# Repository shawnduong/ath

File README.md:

# ath.ino

ath.ino is a simple circuit board that displays a binary message with LEDs, one nibble at a time. This was my first time creating a PCB and this project mainly serves as educational experience and material.

## Images

(The 5V voltage regulator is not needed for this project. It is shown in mine because my Arduino's onboard voltage regulator is broken. See the note at the bottom of this README.)

## Schematic

## Materials

To create this project, you need:

1. 1x Arduino Pro Mini
2. 1x SN74HC595N Shift Register
3. 3x 100 Ohm resistors
   - Other resistor values will substitute just fine depending on the maximum brightness you want for the LEDs.
4. 4x 2n2222 transistors
   - Other transistors can substitute as long as the middle pin is the base.
5. 3x Push buttons
6. 1x Micro slide switches
7. 1x 4x AAAA battery holder
8. 4x RGB common cathode LEDs

## Instructions

1. Print the PCB and solder the parts according to the schematics. The schematics can be viewed in a PCB CAD program such as KiCAD.
2. Upload the code in `src/ath.ino`. Change the `byte sequence[]` variable to be your desired values.

## Usage

Power the LED on by flipping the power switch (PSW0). Dim the R, G, and B levels by pushing SW0, SW1, and SW2, respectively. After reaching the minimum dimness level, the color channel will loop back to the maximum.

## Note

If the onboard voltage regulator in the Arduino is broken, you can connect a 5V voltage regulator the VIN/GND of the Arduino and connect Vout to the 5V line in the Arduino.

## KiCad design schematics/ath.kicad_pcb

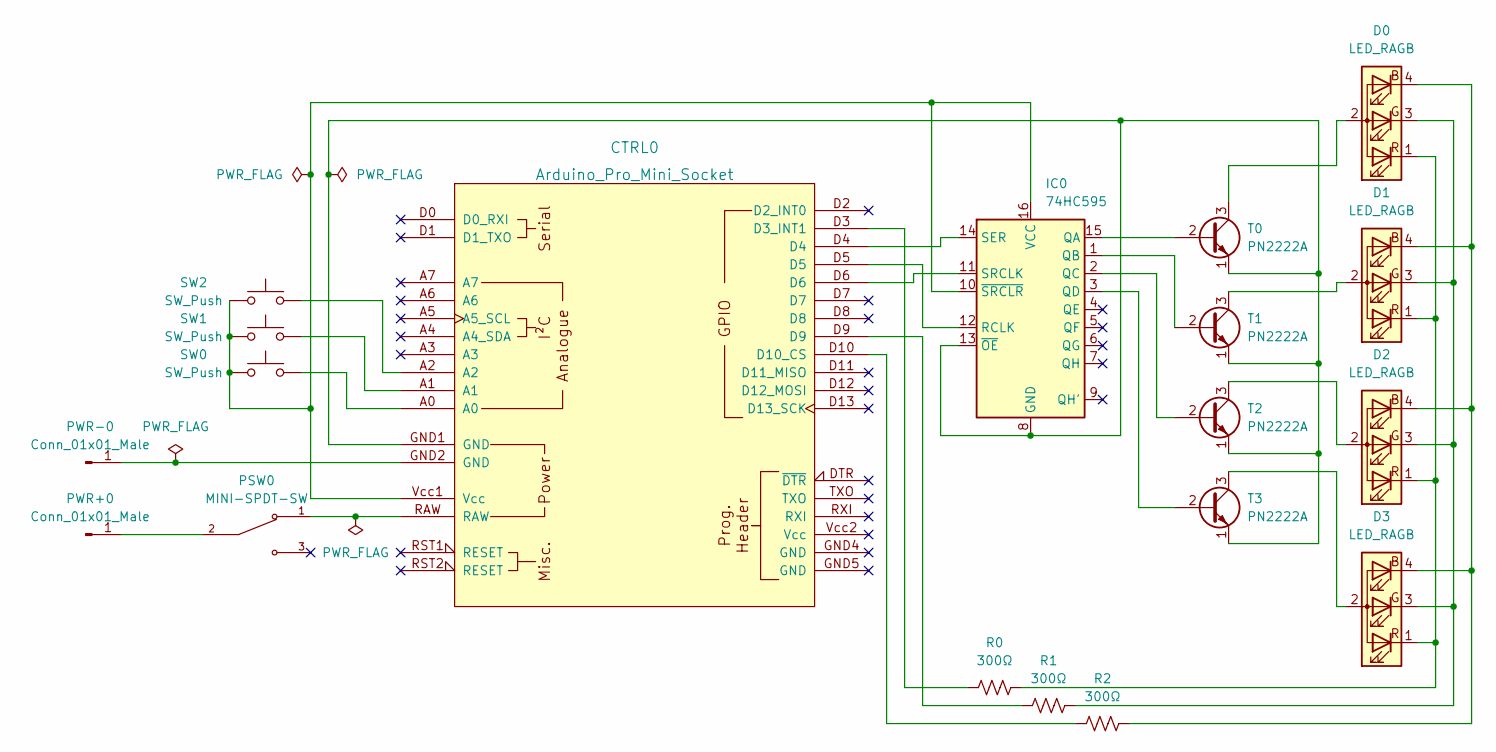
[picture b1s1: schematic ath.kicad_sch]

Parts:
CTRL0: Arduino_Pro_Mini_Socket
D0, D1, D2, D3: LED_RAGB; LED_D5.0mm-4_RGB_Wide_Pins
IC0: 74HC595; DIP794W45P254L1969H508Q16
PSW0: MINI-SPDT-SW; SW_MINI-SPDT-SW; PARTREV C
PWR+0: Conn_01x01_Male; TestPoint_Pad_D2.0mm
PWR-0: Conn_01x01_Male; TestPoint_Pad_D2.0mm
R0, R1, R2: 300Ω; R_Axial_DIN0204_L3.6mm_D1.6mm_P7.62mm_Horizontal
SW0, SW1, SW2: SW_Push; SW_PUSH_6mm_H4.3mm
T0, T1, T2, T3: PN2222A; TO-92_Inline

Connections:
unnamed: CTRL0.A0, SW0.2
unnamed: CTRL0.A1, SW1.2
unnamed: CTRL0.A2, SW2.2
unnamed: CTRL0.D3 (D3_INT1), R0.1
unnamed: CTRL0.D4, IC0.14 (SER)
unnamed: CTRL0.D5, IC0.12 (RCLK)
unnamed: CTRL0.D6, IC0.11 (SRCLK)
unnamed: CTRL0.D9, R1.1
unnamed: CTRL0.D10 (D10_CS), R2.1
unnamed: CTRL0.GND1 (GND), IC0.8 (GND), IC0.13 (~OE), T0.1 (E), T1.1 (E), T2.1 (E), T3.1 (E)
unnamed: CTRL0.GND2 (GND), PWR-0.1
unnamed: CTRL0.RAW, PSW0.1
unnamed: CTRL0.Vcc1 (Vcc), IC0.10 (~SRCLR), IC0.16 (VCC), SW0.1, SW1.1, SW2.1
unnamed: D0.1 (RK), D1.1 (RK), D2.1 (RK), D3.1 (RK), R0.2
unnamed: D0.2 (A), T0.3 (C)
unnamed: D0.3 (GK), D1.3 (GK), D2.3 (GK), D3.3 (GK), R1.2
unnamed: D0.4 (BK), D1.4 (BK), D2.4 (BK), D3.4 (BK), R2.2
unnamed: D1.2 (A), T1.3 (C)
unnamed: D2.2 (A), T2.3 (C)
unnamed: D3.2 (A), T3.3 (C)
unnamed: IC0.1 (QB), T1.2 (B)
unnamed: IC0.2 (QC), T2.2 (B)
unnamed: IC0.3 (QD), T3.2 (B)
unnamed: IC0.15 (QA), T0.2 (B)
unnamed: PSW0.2, PWR+0.1

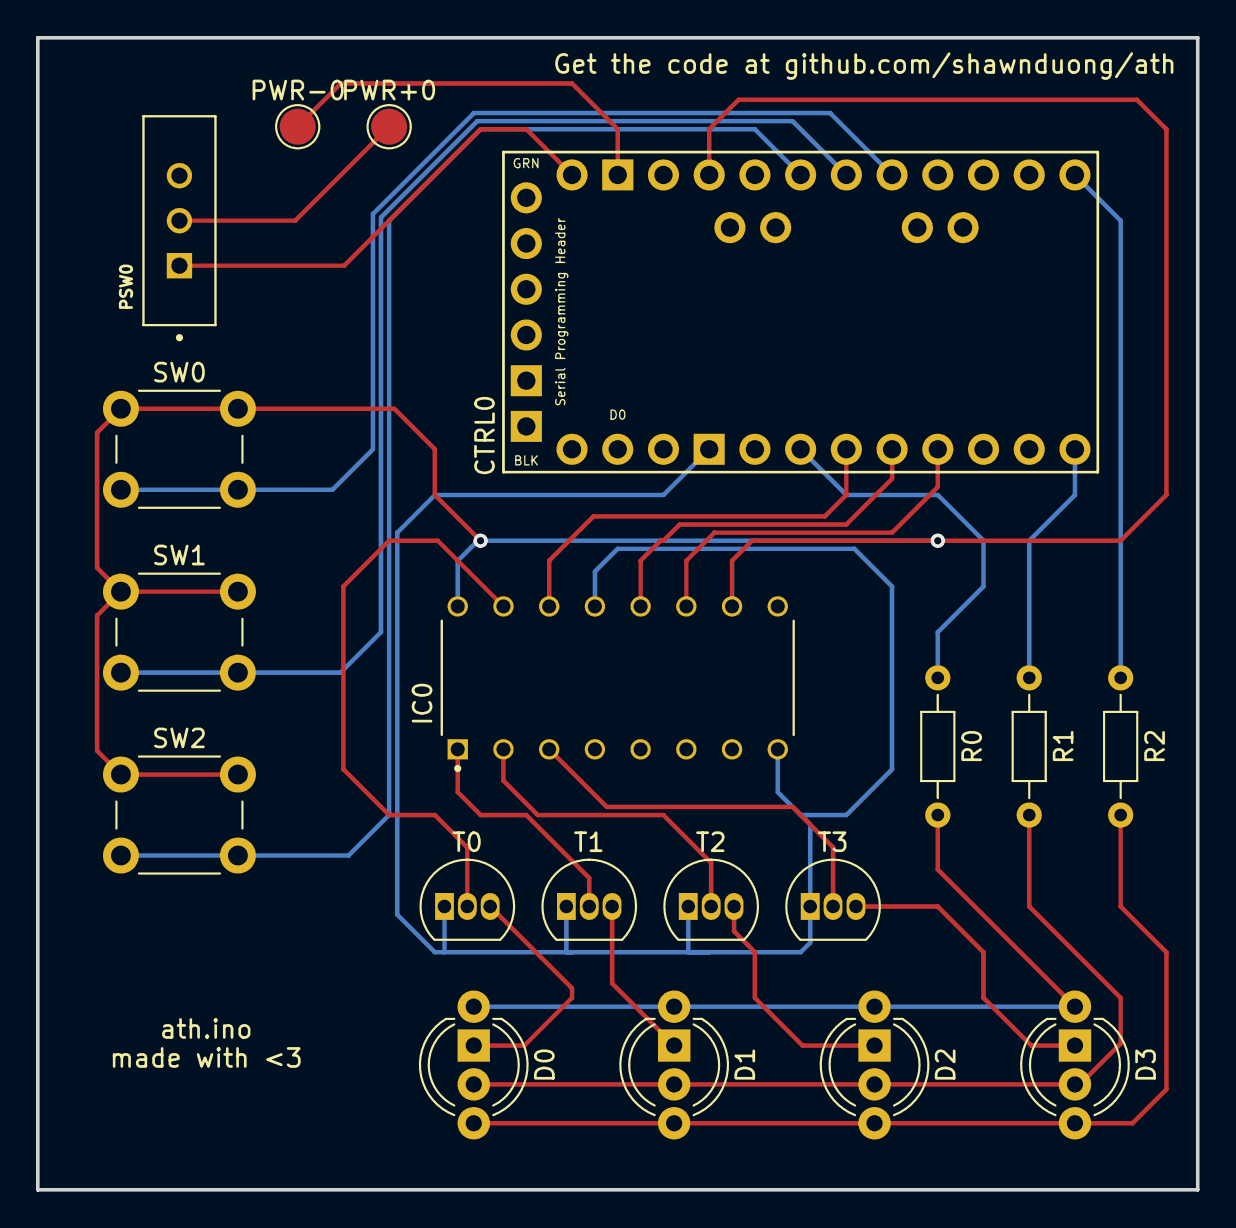
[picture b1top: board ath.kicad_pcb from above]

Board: 2 copper layers, 64.4 x 64.0 mm, 19 parts (0 on the bottom side), 25 nets.

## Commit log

2023-02-14 Uploaded code.
2023-02-14 Moved source code into its own folder.
2023-02-14 Added schematics.
2023-02-14 Uploaded README.md.
2023-02-14 Removed unnecessary KiCAD backups.
2023-02-14 Changed sample sequence to 4 bits each.
